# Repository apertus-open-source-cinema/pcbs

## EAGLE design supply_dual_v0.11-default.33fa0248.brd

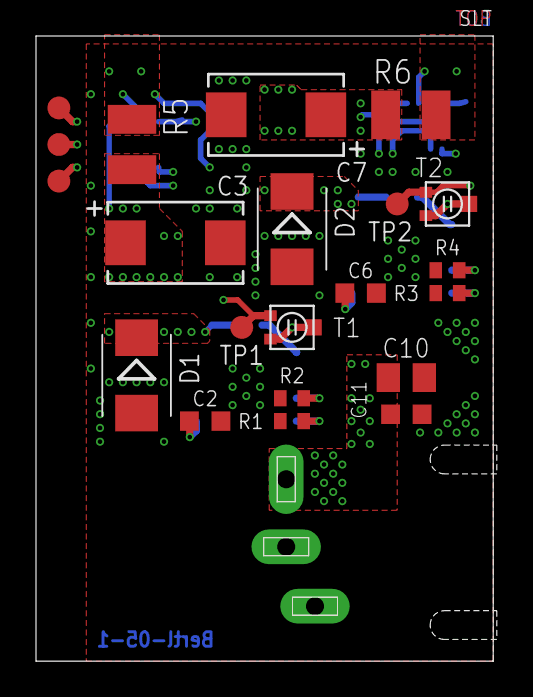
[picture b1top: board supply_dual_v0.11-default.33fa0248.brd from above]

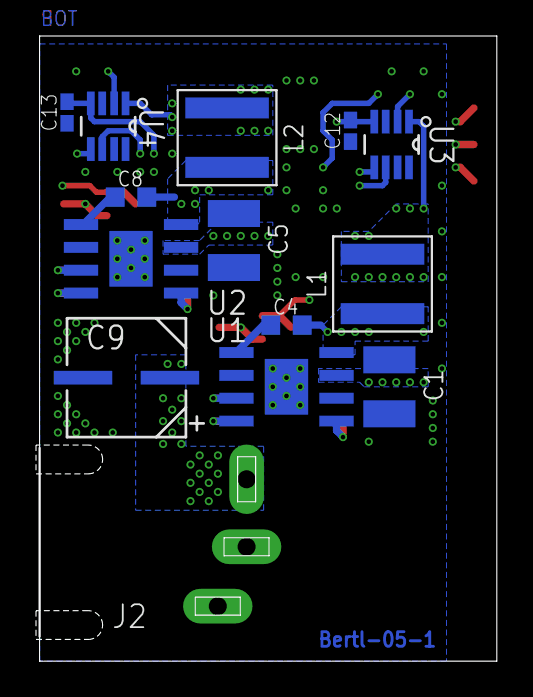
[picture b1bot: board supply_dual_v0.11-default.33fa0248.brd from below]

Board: 4 copper layers, 25.4 x 34.7 mm, 35 parts (14 on the bottom side), 19 nets.

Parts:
C1, C5: 6µ8; C1210K
C2, C6: 1µ; C0603K
C3, C7: 150UF; CAPT7343X430N
C4, C8: 10n; C0603K
C9: 47UF; CAPAE660X610N
C10: 1µ; C0805K
C11: 100n; C0603K
C12, C13: C0402K
D1, D2: SSB4; DO-214AA
J2: FC681485
L1, L2: 8.2µ; XAL50X0
R1, R3: 1k; R0402
R2, R4: 12k4; R0402
R5, R6: 15m; R1210
T1, T2: PVZ2A; TRIM-PVZ2A
TP1, TP2, TP3, TP4, TP5: TPB1,27; B1,27
U1, U2: LM22670; DDA0008B
U3, U4: INA219BIDCNT; SOT65P280X145-8N

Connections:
+3V3: C12.1, C13.1, TP5.TP, U3.4, U4.4
GND: C1.1, C2.1, C3.2, C5.1, C6.1, C7.2, C9.2, C10.1, C11.1, C12.2, C13.2, D1.A, D2.A, J2.2, R1.1, R2.1, R3.1, R4.1, U1.6, U1.EPAD, U2.6, U2.EPAD, U3.3, U4.3
L1O: C3.1, L1.2, R5.1, U3.1
L1P: C4.2, D1.C, L1.1, U1.8
L2O: C7.1, L2.2, R6.1, U4.1
L2P: C8.2, D2.C, L2.1, U2.8
unnamed: R1.2, T1.2, T1.3, U1.4
unnamed: R3.2, T2.2, T2.3, U2.4
unnamed: C8.1, U2.1
unnamed: R4.2, U2.3
unnamed: C6.2, U2.5
unnamed: C4.1, U1.1
unnamed: R2.2, U1.3
unnamed: C2.2, U1.5
OUT1: R5.2, T1.1, TP1.TP, U3.2
OUT2: R6.2, T2.1, TP2.TP, U4.2
SCL1: TP4.TP, U3.5, U4.5
SDA1: TP3.TP, U3.6, U4.6
VIN: C1.2, C5.2, C9.1, C10.2, C11.2, J2.1, U1.7, U2.7
